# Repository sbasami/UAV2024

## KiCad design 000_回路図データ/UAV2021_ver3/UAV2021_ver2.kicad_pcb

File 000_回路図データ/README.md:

# 回路図データ
* BMI088_ver2: BMI088モジュール基板のKiCad回路データ
* UAV2021_ver3: フライトコントローラ基板のKiCad回路データ
* UAV2021_ver3_panelizing: BMI088_ver2とUAV2021_ver3を面付けしたPCBデータとガーバーデータ(このデータを使って基板製造業者に発注)

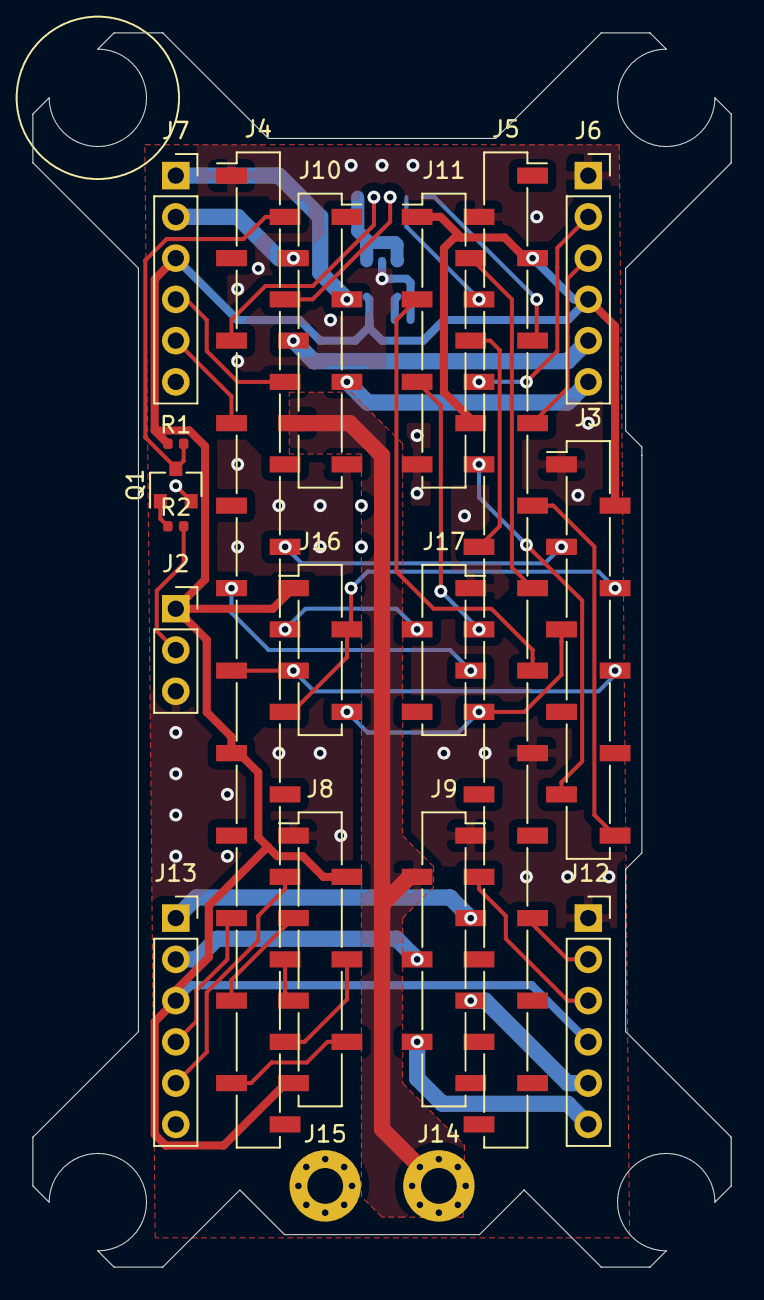
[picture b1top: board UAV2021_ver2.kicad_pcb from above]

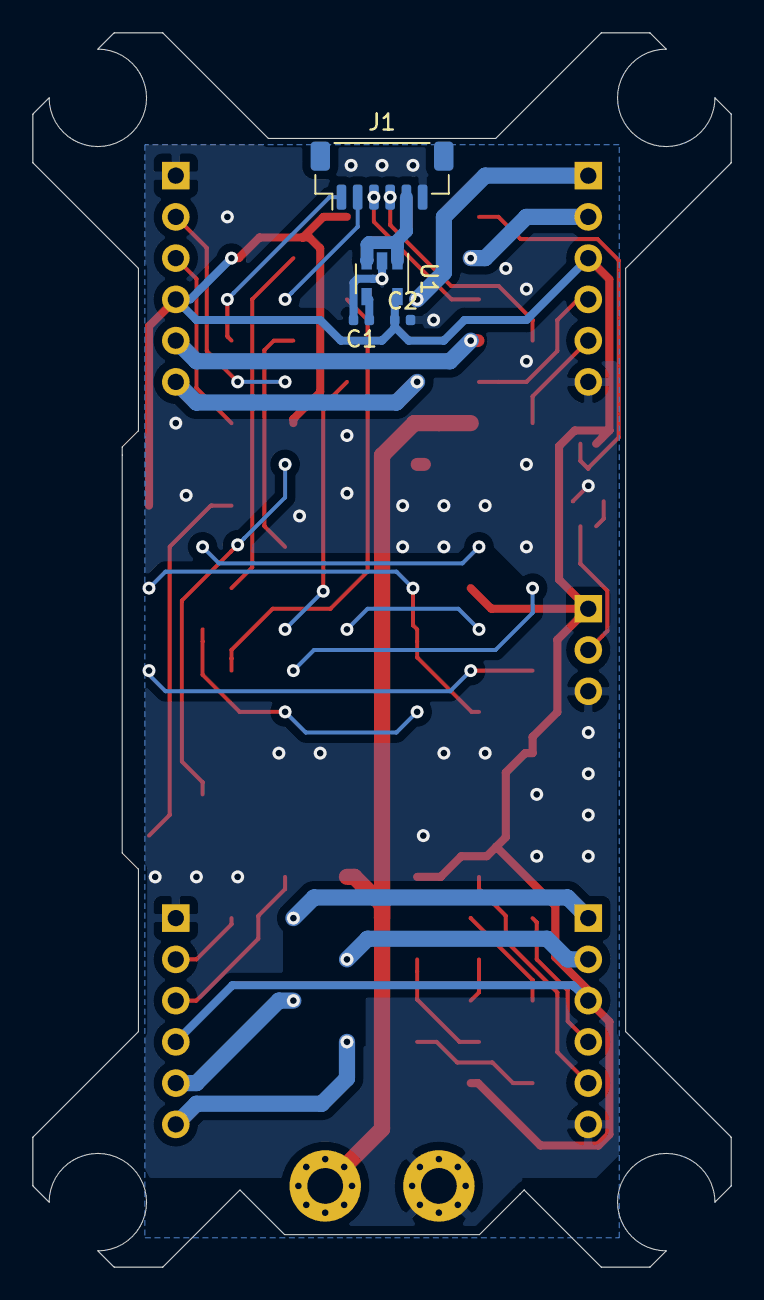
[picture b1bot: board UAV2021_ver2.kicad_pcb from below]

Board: 2 copper layers, 43.0 x 76.0 mm, 23 parts (4 on the bottom side), 44 nets.

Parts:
C1: 470p; C_0402_1005Metric
C2: 2.2u; C_0402_1005Metric
J1: Conn_01x06; JST_SH_BM06B-SRSS-TB_1x06-1MP_P1.00mm_Vertical
J2: Conn_01x03; PinSocket_1x03_P2.54mm_Vertical
J3: Conn_01x10; PinSocket_1x10_P2.54mm_Vertical_SMD_Pin1Left
J4: Conn_01x24; PinSocket_1x24_P2.54mm_Vertical_SMD_Pin1Left
J5: Conn_01x24; PinSocket_1x24_P2.54mm_Vertical_SMD_Pin1Right
J6, J7, J12, J13: Conn_01x06; PinSocket_1x06_P2.54mm_Vertical
J8, J11: Conn_01x07; PinSocket_1x07_P2.54mm_Vertical_SMD_Pin1Left
J9, J10: Conn_01x07; PinSocket_1x07_P2.54mm_Vertical_SMD_Pin1Right
J14, J15: Conn_01x01; MountingHole_2.2mm_M2_Pad_Via
J16: Conn_01x04; PinSocket_1x04_P2.54mm_Vertical_SMD_Pin1Left
J17: Conn_01x04; PinSocket_1x04_P2.54mm_Vertical_SMD_Pin1Right
Q1: 2N7002K; SOT-23
R1: 10k; R_0402_1005Metric
R2: 3.3k; R_0402_1005Metric
U1: MIC5219-3.3YM5; SOT-23-5

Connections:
+3V3: C2.1, J2.1, J3.2, J4.15, J5.3, J6.4, J7.3, J8.2, J8.7, J11.1, J11.6, J12.4, J13.3, J16.1, R1.1, U1.5
+7.5V: J1.5, U1.1, U1.3
/Sheet60DC4E71/RCV_IN: J2.2, R2.2
AENBL_1: J5.13, J11.3
AENBL_2: J4.20, J8.5
APHAZE_1: J5.11, J11.2
APHAZE_2: J4.23, J8.6
BENBL_1: J5.12, J11.5
BENBL_2: J4.21, J8.3
BPHAZE_1: J5.10, J11.4
BPHAZE_2: J4.22, J8.4
CS_A: J4.12, J17.2
CS_G: J4.11, J17.3
CS_O: J3.3, J4.10
FUTABA: J4.2, Q1.3, R1.2
GND: C1.2, C2.2, J1.6, J2.3, J3.1, J4.1, J5.2, J5.15, J6.1, J7.6, J8.1, J9.1, J10.7, J11.7, J12.1, J13.6, J15.1, J17.1, Q1.2, U1.2
M1_1: J6.6, J10.5
M1_2: J9.6, J12.6
M1_3: J9.3, J13.1
M1_4: J7.1, J10.3
M2_1: J6.5, J10.4
M2_2: J9.5, J12.5
M2_3: J9.4, J13.2
M2_4: J7.2, J10.2
MISO: J3.4, J4.14, J16.2
MOSI: J3.6, J4.13, J16.3
unnamed: C1.1, U1.4
unnamed: Q1.1, R2.1
OUTA_1: J5.7, J6.3
OUTA_2: J5.18, J12.3
OUTA_3: J4.19, J13.4
OUTA_4: J4.6, J7.4
OUTB_1: J5.6, J6.2
OUTB_2: J5.19, J12.2
OUTB_3: J4.18, J13.5
OUTB_4: J4.7, J7.5
PWM_1: J1.1, J5.5
PWM_2: J1.2, J5.4
PWM_3: J1.3, J4.4
PWM_4: J1.4, J4.5
SCK: J3.5, J5.14, J16.4
SCL: J3.9, J5.8
SDA: J3.10, J5.9
VCC: J9.2, J10.6, J14.1

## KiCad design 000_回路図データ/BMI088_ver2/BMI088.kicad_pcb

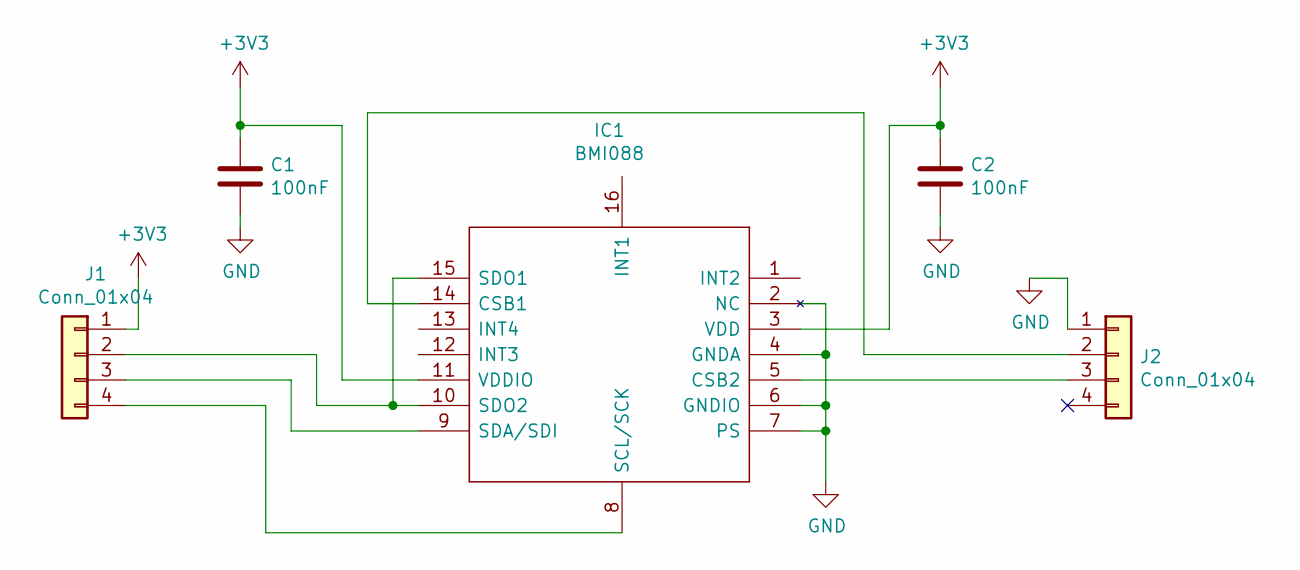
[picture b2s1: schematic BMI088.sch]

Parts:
C1, C2: 100nF; C_0402_1005Metric
IC1: BMI088; Manufacturer_Part_Number BMI088
J1, J2: Conn_01x04; PinHeader_1x04_P2.54mm_Vertical

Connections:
+3V3: C1.1, C2.1, IC1.3 (VDD), IC1.11 (VDDIO), J1.1
GND: C1.2, C2.2, IC1.2 (NC), IC1.4 (GNDA), IC1.6 (GNDIO), IC1.7 (PS), J2.1
unnamed: IC1.5 (CSB2), J2.3
unnamed: IC1.8 (SCL/SCK), J1.4
unnamed: IC1.9 (SDA/SDI), J1.3
unnamed: IC1.10 (SDO2), IC1.15 (SDO1), J1.2
unnamed: IC1.14 (CSB1), J2.2

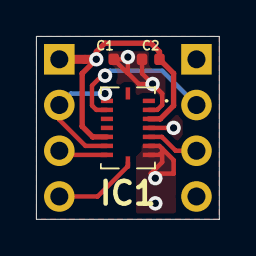
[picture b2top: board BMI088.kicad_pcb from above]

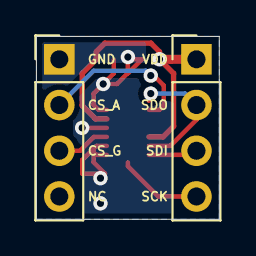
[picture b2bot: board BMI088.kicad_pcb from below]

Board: 2 copper layers, 10.2 x 10.2 mm, 5 parts (2 on the bottom side), 7 nets.

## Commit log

2024-07-15 回路図データを追加
    追加したデータがそれぞれ何なのかは000_回路図データフォルダ内のREADME.mdを参照
2024-07-21 3Dデータを追加
2024-08-17 PlatformIOでTeensy4.1用のプロジェクトを作成
2024-08-17 Clang-formatの追加
2024-08-17 Cppcheckで静的解析を実施する設定を追加
    Platform IOはデフォルトで暗黙的にCppcheckで静的解析を実施するようになっているが明示的に設定
    詳細は下記参照
    https://docs.platformio.org/en/latest//advanced/static-code-analysis/tools/cppcheck.html
2024-08-25 Clang-formatルール更新、Clang Format Editorにアップロードする用のファイル(clamg-format)追加
2024-08-26 SbusReceiverクラス追加
    Sbusで受信したデータを0~1の範囲のデータに変換して提供する
2024-08-27 cppcheckの指摘修正
    Class 'SbusReceiver' has a constructor with 1 argument that is not explicit.
2024-08-27 ビルドエラーになったので変数名変更
2024-08-27 不要な定義削除、defineをconstexprに変更
2024-08-30 ServoEncoderクラス追加
    エンコーダで取得した値をdeg or radの単位で提供する
2024-08-31 ServoDriverクラス追加
    Dutyを-1~1の範囲で設定しPWM出力する
2024-08-31 ServoControllerクラス追加
    目標角度[rad]、現在角度[rad]、電源電圧[V]からDuty[-1~1]を計算する
2024-08-31 Servo関係の処理をservo.cppに集約
2024-09-01 cppcheckの指摘修正
2024-09-21 AttitudeSensorクラス追加
    センサ情報から機体の姿勢を計算するクラス
2024-09-22 ThrustDriverクラス、ThrustControllerクラス追加、Thrust関係の処理をthrust.cppに集約
    ThrustDriverクラス：Dutyを0~1の範囲で設定しPWM出力する
    ThrustControllerクラス：推力[N]をDuty[0-1]に変換する(現状は入力値を0-1で制限する機能のみ)
2024-11-04 ServoDriverに回転方向を変更する機能を追加
    回路的に1つだけモータの接続が反転しているため4つのモータに同じ信号を送った時に1つだけ反対方向に回転していた。
    ハードの差を吸収できるようにソフト的に回転方向を指定できる機能を追加。
2024-12-01 AttitudeControllerクラス
    目標姿勢と現在姿勢の回転行列から誤差回転行列を計算し、PID制御の制御量を計算する
2024-12-01 AttitudePlannerクラス追加
    プロポの信号と現在姿勢から目標姿勢を計算する
2024-12-01 PositionControllerクラス追加
    位置の制御量を計算する
2024-12-01 Distributorクラス
    位置と姿勢の操作量をモータ推力とサーボ角度に変換する
2024-12-01 ドローン制御関係の処理をdrone.cppに集約
2024-12-01 main.cをドローン制御用に変更(この時点で一応飛行できる)
2024-12-01 Yaw軸Pゲインを調整
2024-12-14 位置の制御量を座標変換する機能を追加
    姿勢が傾いても操作感覚が変わらないように位置の制御量を姿勢で座標変換
2025-02-11 目標姿勢をランプ上に変化させる機能を追加
2025-02-11 加速度センサの初期化失敗の対策
2025-02-11 プロポのY軸制御の座標系が間違っていたので修正
    プロポの操作に対する操作量の変化の方向が変わったのでプログラム側も修正
2025-02-12 チルト飛行に関連するパラメータのIF関数追加
2025-02-15 コメント追加変更
